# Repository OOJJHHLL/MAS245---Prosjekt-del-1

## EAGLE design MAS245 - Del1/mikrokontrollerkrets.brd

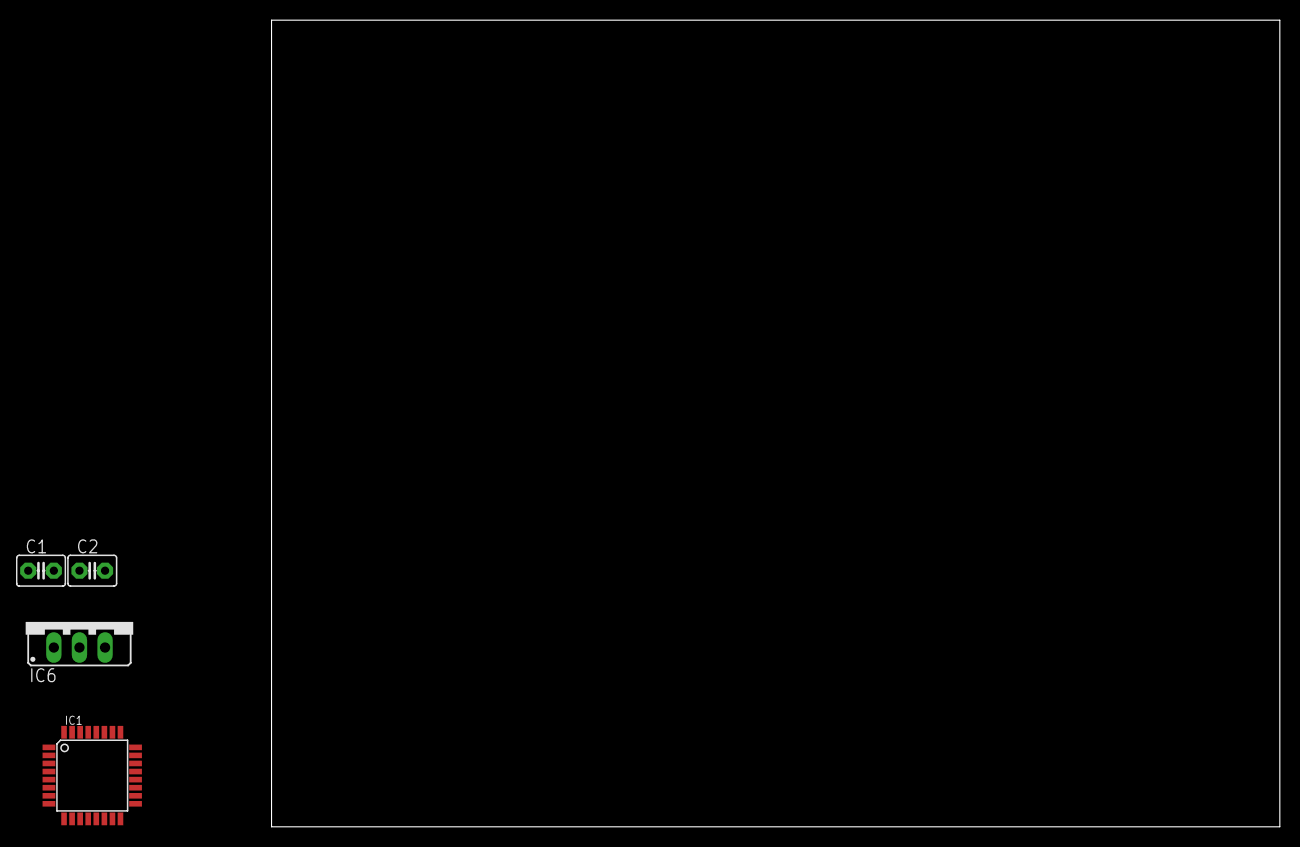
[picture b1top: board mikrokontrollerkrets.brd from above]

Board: 2 copper layers, 100.0 x 80.0 mm, 4 parts (0 on the bottom side), 5 nets, no tracks yet.

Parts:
C1: 0.1; C2.5-3
C2: 100μF; C2.5-3
IC1: MEGA8-AI; TQFP32-08
IC6: LM2931T; TO220S

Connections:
+5V: C2.1, IC6.3
+24V: C1.1, IC6.1
GND: IC1.3, IC1.5, IC1.21
GNDA: C1.2, C2.2, IC6.2
VCC: IC1.4, IC1.6

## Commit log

2022-10-11 Tester
2022-10-11 Add files via upload
    Tester en pull
2022-10-11 Dytter den opp igjen
2022-10-12 Added Thomas :)
2022-10-14 Tegninger
2022-10-19 Added softblink
2022-10-19 Updated softblink
2022-10-21 Oppdatert mikrokontrollerkrets
2022-10-21 Har lagt til UFERDIG knappekrets
2022-10-27 Added Toggle led and other modifications
2022-11-15 La til oppdatert knappekrets. MÅ LEGGE TIL KOBLING TIL DEN HVITE BOKSEN
2022-11-15 La til LED krets
2022-11-15 Softblink project folder
2022-11-15 Update main.cpp
    Updated the softblink script
2022-11-15 Project folder. Controll LED with button
2022-11-15 Updated the code
2022-11-21 SoftBlink with Perceived Light Function
2022-11-21 Added the files inside SOftBlinkPLF for treal this time...
2022-11-21 The code is updated
2022-11-21 Updated the cpp-file
2022-11-22 Last commit
